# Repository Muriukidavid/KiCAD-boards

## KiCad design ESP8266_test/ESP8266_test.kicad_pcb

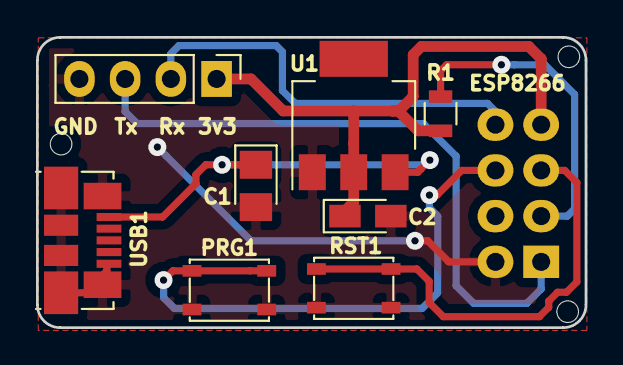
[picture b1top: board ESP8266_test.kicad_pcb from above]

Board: 2 copper layers, 30.5 x 16.1 mm, 12 parts (1 on the bottom side), 8 nets.

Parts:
C1: 0.1uF; CP_Tantalum_Case-R_EIA-2012-12_Reflow
C2: 0.1uF; CP_Tantalum_Case-R_EIA-2012-12_Wave
ESP8266: Conn_02x04_Odd_Even; Socket_Strip_Straight_2x04_Pitch2.54mm
MK1, MK2, MK3: Mounting_Hole; MountingHole_2.2mm_M2
PRG1: SW_SPST; SW_SPST_PTS810
R1: 10K; R_0805
RST1: SW_SPST; SW_SPST_PTS810
U1: LT1117-3.3; SOT-223
UART_COMM1: Conn_01x04; Pin_Header_Straight_1x04_Pitch2.54mm
USB1: USB_B_Micro; USB_Micro-B_Molex_47346-0001

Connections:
3v3: C2.1, ESP8266.7, R1.1, U1.2, UART_COMM1.1
CH_EN: ESP8266.3, R1.2
GND: C1.2, C2.2, ESP8266.2, PRG1.2, RST1.2, U1.1, UART_COMM1.4, USB1.5, USB1.6
GPIO0: ESP8266.6, PRG1.1
unnamed: C1.1, U1.3, USB1.1
RST: ESP8266.5, RST1.1
Rx: ESP8266.8, UART_COMM1.2
Tx: ESP8266.1, UART_COMM1.3

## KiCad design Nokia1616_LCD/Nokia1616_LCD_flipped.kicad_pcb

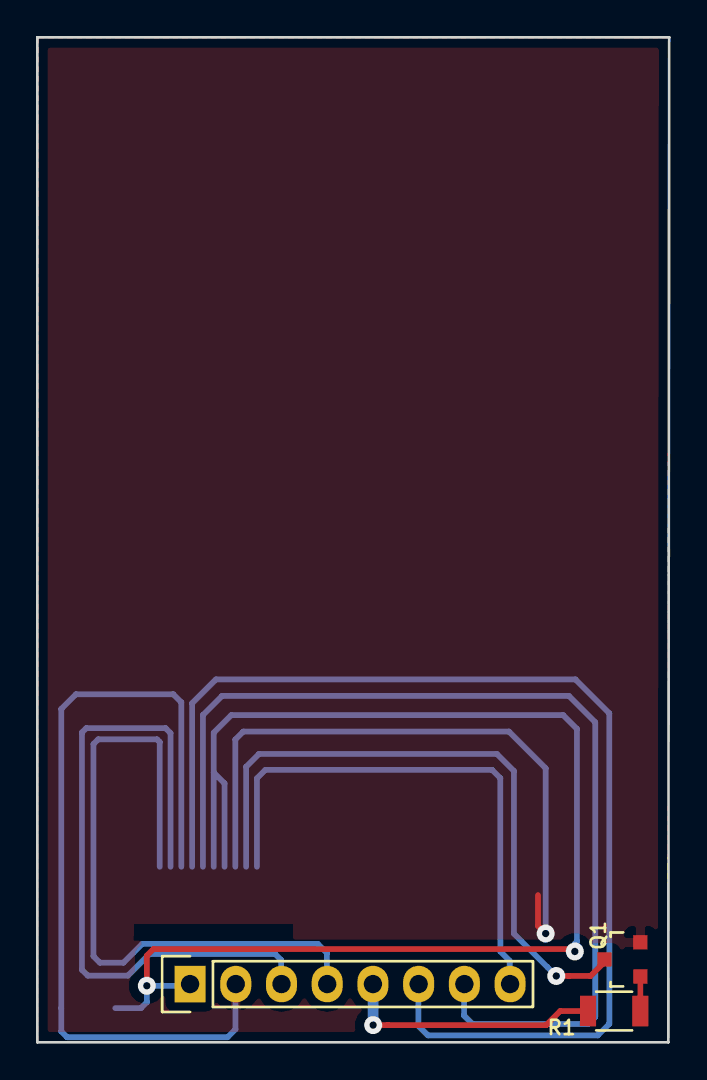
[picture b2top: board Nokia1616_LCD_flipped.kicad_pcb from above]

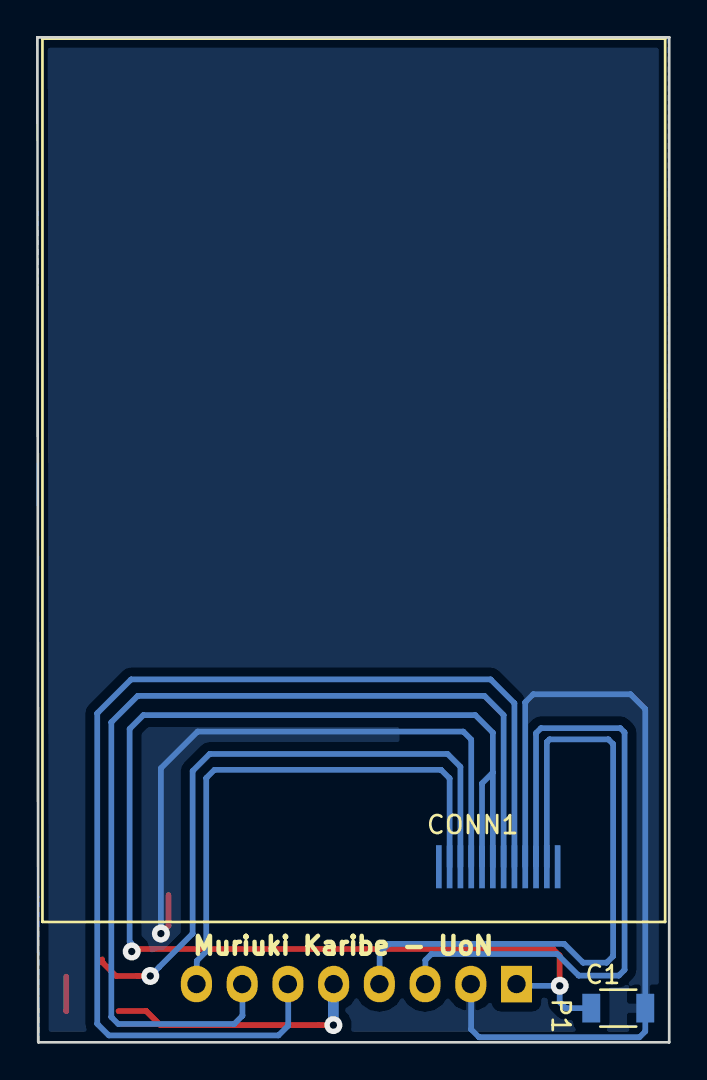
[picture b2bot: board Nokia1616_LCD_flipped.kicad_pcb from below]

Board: 2 copper layers, 35.1 x 55.8 mm, 5 parts (2 on the bottom side), 10 nets.

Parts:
C1: 0.1; C_1206
CONN1: Nokia1616_LCD
P1: CONN_01X08; Pin_Header_Straight_1x08
Q1: BC547_BEC_123; SOT-23
R1: 1K; R_1206

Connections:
5V: CONN1.11, P1.8
CE: CONN1.3, P1.3
CLK: CONN1.6, P1.7
GND: C1.2, CONN1.4, CONN1.9, P1.2, Q1.2
LED: P1.5, R1.2
LED-: CONN1.10, Q1.3
MOSI: CONN1.5, P1.6
unnamed: Q1.1, R1.1
RESET: CONN1.2, P1.4
VCC: C1.1, CONN1.7, CONN1.8, P1.1

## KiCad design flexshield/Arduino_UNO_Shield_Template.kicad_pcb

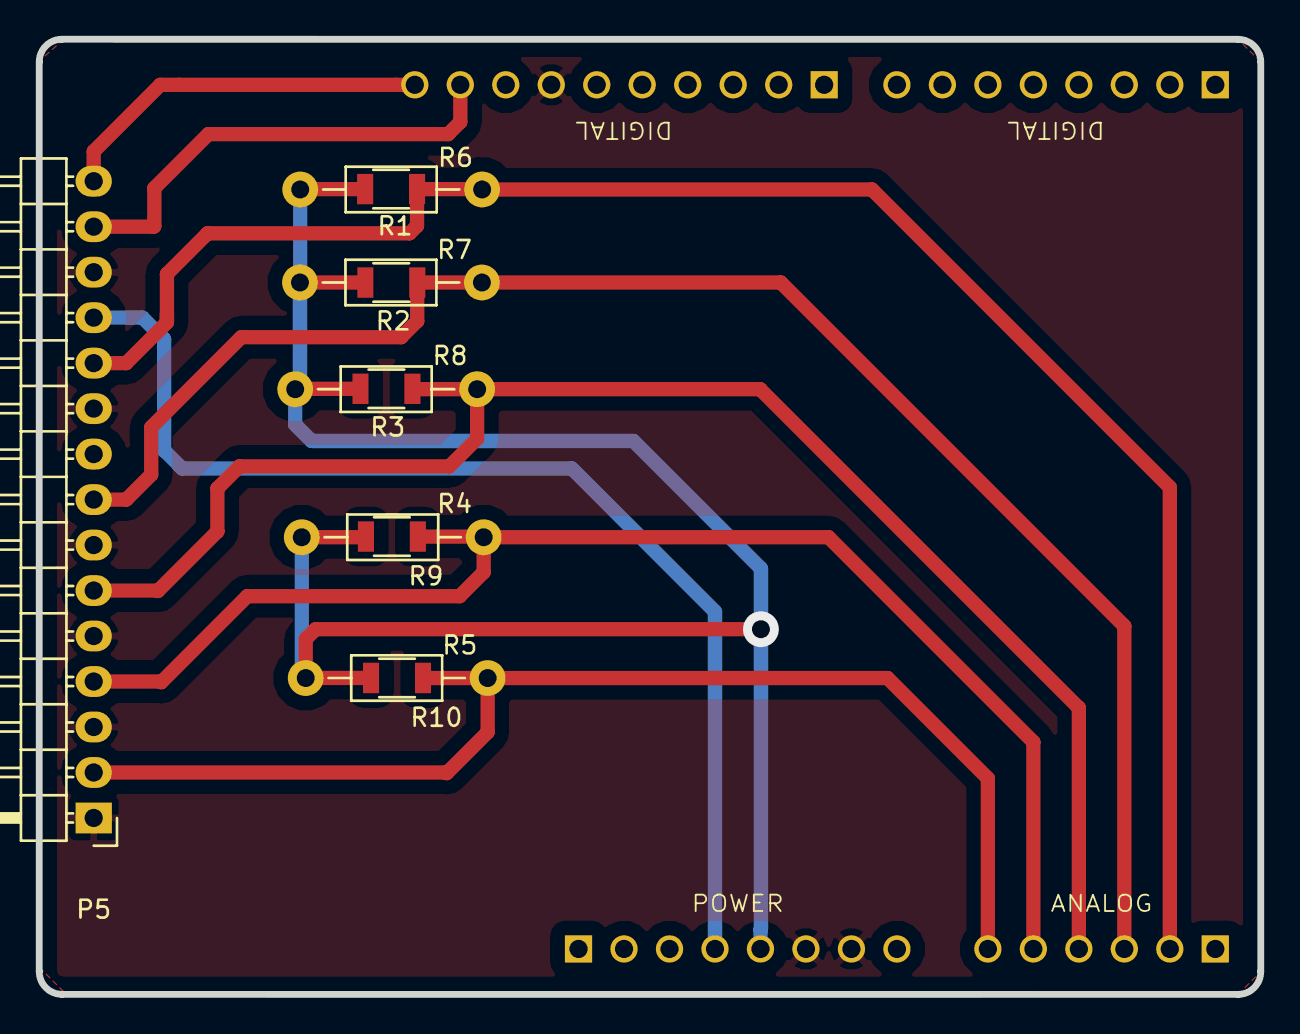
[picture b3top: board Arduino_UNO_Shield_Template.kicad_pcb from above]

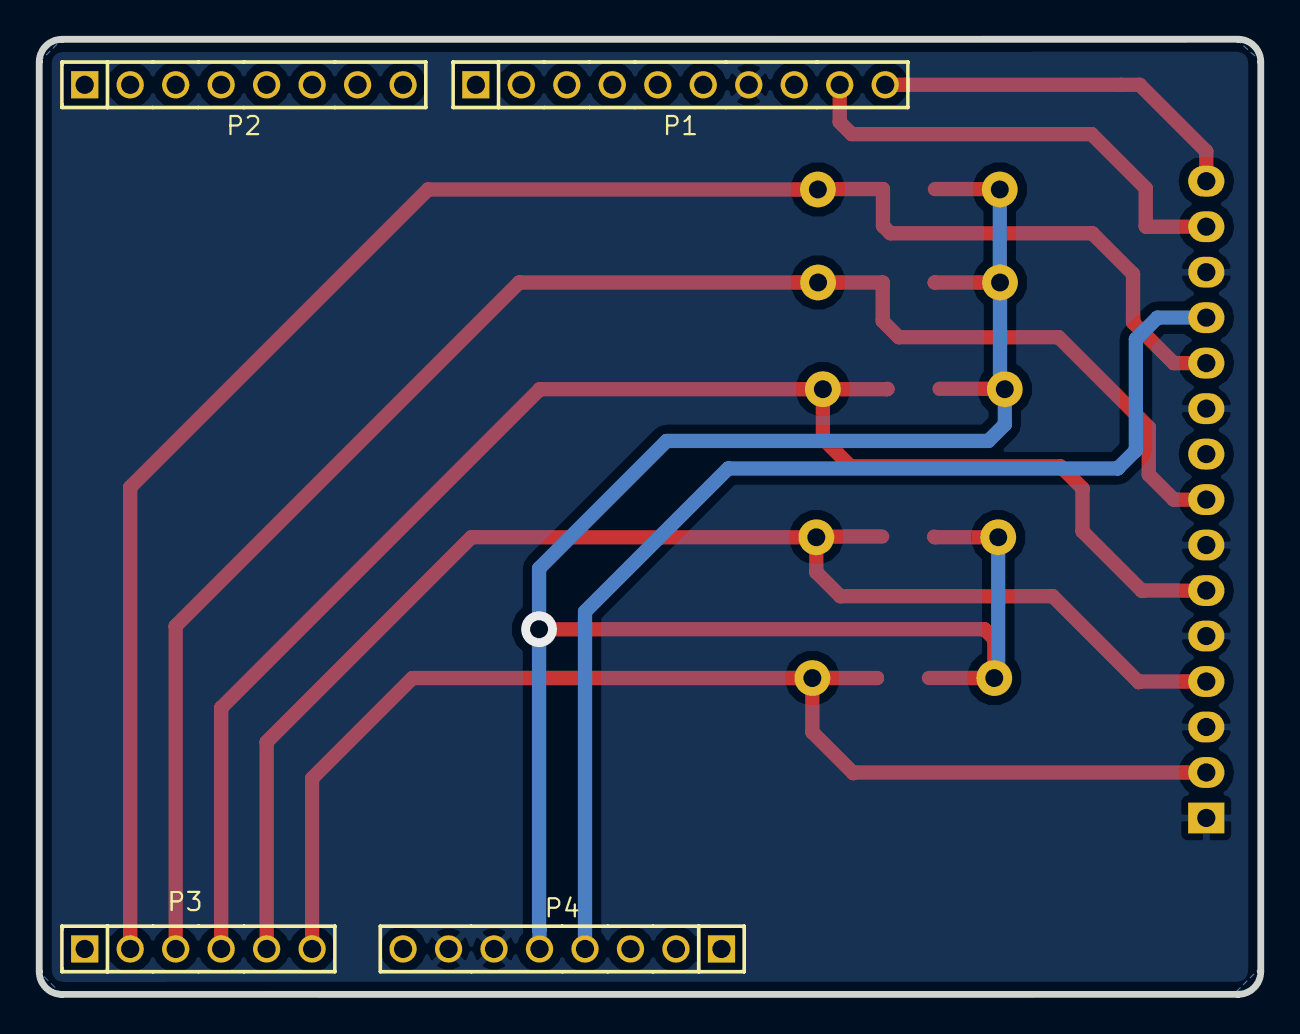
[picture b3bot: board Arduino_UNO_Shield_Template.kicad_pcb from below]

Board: 2 copper layers, 68.2 x 53.3 mm, 15 parts (4 on the bottom side), 10 nets.

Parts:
P1: HEADER_M_2.54MM_1R10P_ST_AU_PTH
P2, P4: HEADER_M_2.54MM_1R8P_ST_AU_PTH
P3: HEADER_M_2.54MM_1R6P_ST_AU_PTH
P5: CONN_01X15; Pin_Header_Angled_1x15
R1, R2, R3, R4, R5: R; Resistor_Horizontal_RM10mm
R6, R7, R8, R9, R10: R; R_1206

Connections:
3.3V: P4.4, P5.12
5V: P4.5, R1.2, R2.2, R3.2, R4.2, R5.2, R6.2, R7.2, R8.2, R9.2, R10.2
AD0: P3.6, P5.2, R5.1, R10.1
AD1: P3.5, P5.4, R4.1, R9.1
AD2: P3.4, P5.6, R3.1, R8.1
AD3: P3.3, P5.8, R2.1, R7.1
AD4: P3.2, P5.11, R1.1, R6.1
AD4/SDA: P1.9, P5.14
AD5/SCL: P1.10, P5.15
GND: P1.7, P4.6, P4.7, P5.1, P5.3, P5.5, P5.7, P5.10, P5.13

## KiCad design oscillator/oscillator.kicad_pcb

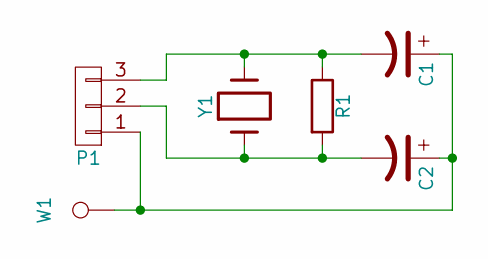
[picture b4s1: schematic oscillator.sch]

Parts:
C1, C2: CP1; C_1206
P1: CONN_01X03; Pin_Header_Angled_1x03
R1: R; R_1206
W1: TEST_1P; Pin_Header_Straight_1x01
Y1: Crystal; Crystal_FOX-FE_SMD

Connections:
unnamed: C1.1, C2.1, P1.1, W1.1
unnamed: C1.2, P1.3, R1.1, Y1.2
unnamed: C2.2, P1.2, R1.2, Y1.1

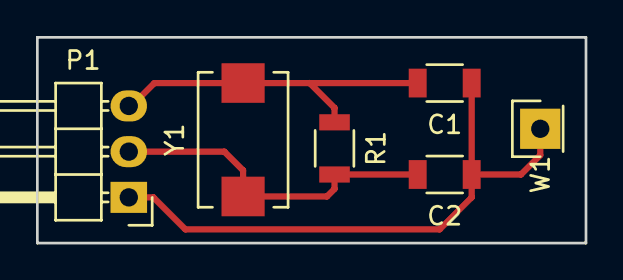
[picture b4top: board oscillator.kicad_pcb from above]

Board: 2 copper layers, 30.5 x 11.4 mm, 6 parts (0 on the bottom side), 3 nets.

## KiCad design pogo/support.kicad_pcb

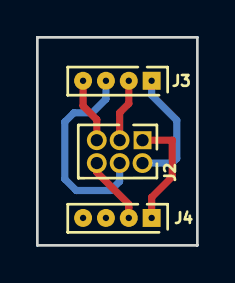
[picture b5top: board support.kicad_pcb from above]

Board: 2 copper layers, 8.9 x 11.6 mm, 3 parts (0 on the bottom side), 6 nets.

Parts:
J2: CONN_02X03; Pin_Header_Pogo_02x03_Pitch1.27mm
J3, J4: CONN_01X04; Pin_Header_Straight_01x04_Pitch1.27mm

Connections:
3v3: J2.1, J4.1
GND: J2.6, J4.2
RESET: J2.5, J3.4
SWDCLK: J2.3, J3.2
SWDIO: J2.2, J3.1
SWDTRACE: J2.4, J3.3
